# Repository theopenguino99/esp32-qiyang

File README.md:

<div align="center">

**On-device firmware for the crimp-ER hangboard scale — ESP32-C6, HX711 load cell, OLED readout &amp; live force streaming over BLE.**

</div>

---

# ESP32-C6 Smart Load Cell

Firmware for an ESP32-C6 based digital scale. Reads an HX711 load cell, shows live
weight on a 1.3" OLED, streams readings over BLE, and supports on-device
calibration with 2 push buttons. It speaks the **Tindeq Progressor** BLE protocol,
so it works with the official Tindeq app as well as the companion web app. I initially wanted to create an IOS app but realised I have to pay a premium to enroll in the Apple Developer Program in order to make the app public, so I made a web app instead which is free. My motivation for creating this project was to practice my software and hardware skills, and to build a useful tool for climbers. My gripe about the tindeq progressor is that it is quite expensive for what essentially is just a load cell so I decided to make one of my own and learn some skills along the way. This project was also something to keep me busy while I undergo ACL surgery rehabilitation. 

I would like to thank Yu Jie for helping me 3D print the prototype enclosure. I also want to thank [@SergioGasquez](https://github.com/SergioGasquez) for giving advice to build the device. I took quite a bit of inspiration from his project [Crimpdeq](https://github.com/crimpdeq).

Some important firmware modifications I made was to use a C6 module instead of a C3 rust module because I wanted to learn how to use a C6 for other future projects as it is one of the more powerful boards by espressif. Also I am using the platformio manager and writing the main firmware in arduino code simple for other beginner to intermediate developers. I also added 2 buttons for user friendly calibration if ever the user does not want to use the webapp or tindeq app. Also I implemented an OLED screen to visualise a force graph. Some things that I can potentially do in the future is a flappy bird game displayed on the OLED. These design choices were made with the possibility of further improvement without re-printing the PCB in mind. 

## Hardware

| Peripheral        | Connection                          |
|-------------------|-------------------------------------|
| HX711 load cell   | DT = GPIO11, SCK = GPIO10           |
| SH1106 OLED (I2C) | SDA = GPIO6, SCL = GPIO7, addr 0x3C |
| WS2812B RGB LED   | GPIO8 (onboard)                     |
| Button 1          | GPIO2 (active-low, internal pullup) |
| Button 2          | GPIO3 (active-low, internal pullup) |

All hardware design files live in [`hardware/`](hardware/) — KiCad project,
gerbers (`hardware/fab/`), and the 3D-printable enclosure.

### PCB

Custom 2-layer board designed in KiCad ([`hardware/pcb_Crimp-ER.kicad_pcb`](hardware/pcb_Crimp-ER.kicad_pcb)).

| Front | Back | Actual|
|:-----:|:----:|:-----:|
|  |  |  |

### Enclosure

Two-part 3D-printed case. Models (STL + STEP) live in
[`hardware/crimp-ER covers/`](hardware/crimp-ER%20covers/).

|Full Assembly| Top cover | Bottom cover |
|:---------:|:------------:|:-:|
||  |  |

> Print-ready downloads:
> [top STL](hardware/crimp-ER%20covers/top_cover.stl) ·
> [bottom STL](hardware/crimp-ER%20covers/bottom_cover.stl).

Two buttons drive the on-device UI: **Button 1 = change/skip**, **Button 2 =
OK/confirm**.

**On boot** the OLED shows a `CALIBRATE?` prompt and waits (no time limit) for a
choice:

- **Button 2** → run calibration (see below).
- **Button 1** → skip. If a calibration is saved, the device re-zeros the empty
  scale in memory (a boot tare that cancels power-on drift while keeping the saved
  scale factor); if none is saved, it warns and runs with defaults.

**Calibration**

1. *Pick the weight* — Button 1 cycles the reference-weight presets
   (1.25, 2.5, 5, 8, 10, 15, 20, 25 kg), Button 2 confirms. It starts at your
   last-used weight.
2. *Zero* — keep the scale empty; it samples the offset.
3. *Place weight* — a 30-second countdown appears (large timer + progress bar).
   Put the selected weight on the scale; Button 2 ends the countdown early.
4. The scale factor is computed and saved to flash (offset, scale, and the chosen
   weight), then a result screen shows (3 beeps on success, 1 on failure if the
   reading is invalid).

**Normal operation**

- OLED shows the current weight (large) plus a rolling history graph.
- The RGB LED flashes red while no BLE client is connected.
- Each changed reading is streamed over BLE as `"<weight> kg\n"`.

## BLE

The device advertises as **`Progressor_XXXX`** (`XXXX` derived from the chip MAC)
and exposes two services in parallel.

### Tindeq Progressor (works with the Tindeq app)

Emulates the Tindeq Progressor so the official **Tindeq app** can connect.

- Service: `7e4e1701-1ea6-40c9-9dcc-13d34ffead57`
- Data — notify, device → app: `7e4e1702-…`
- Control — write, app → device: `7e4e1703-…`
- **Weight stream** (little-endian): `[0x01][8][float32 kg][uint32 timestamp_µs]`,
  sent only between *start* and *stop*.
- **Commands:** tare `100`, start `101`, stop `102`, get app version `107`,
  get battery `111`. Tare is a soft, non-persisted re-zero (keeps the saved
  calibration factor).

### Nordic UART Service (web app)

- Service: `6E400001-…`, RX `6E400002-…`, TX `6E400003-…`
- Plain-text TX `"<weight> kg\n"`. Still running, so the companion web app works
  with no changes — it picks devices with `acceptAllDevices`, so the device simply
  shows up as `Progressor_XXXX` (instead of `ESP32-C6`) in the Bluetooth chooser.

A companion web app lives at `../esp32-qiyang-webapp`.

## Build & flash

```bash
pio run -t upload      # build + flash
pio device monitor     # serial @ 115200
pio run                # build only
```

## Licence

This project is dual-licensed by component:

- **Firmware** (`src/`, `include/`) — [MIT](LICENSE).
- **Hardware** (`hardware/`: PCB, gerbers, enclosure) —
  [CERN-OHL-S v2](hardware/LICENSE) (Strongly Reciprocal). See
  [hardware/README.md](hardware/README.md) for the notice.

In both cases please keep the copyright notice and credit theopenguino99.

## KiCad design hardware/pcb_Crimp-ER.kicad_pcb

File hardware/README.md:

# Hardware

PCB and enclosure design files for the esp32-qiyang smart scale.

- `pcb_Crimp-ER.kicad_{pro,sch,pcb}` — KiCad project (schematic + layout).
- `fab/` — gerbers, drill files, pick-and-place, fabrication zip.
- `crimp-ER covers/` — 3D-printed enclosure (`*.stl` + `*.step`).
- `renders/` — PNG/JPEG previews.

## Licence

Copyright theopenguino99.

This hardware design is licensed under the CERN Open Hardware Licence
Version 2 - Strongly Reciprocal (CERN-OHL-S v2). You may redistribute and
modify it under the terms of that licence; you must keep this notice and
distribute the Complete Source of any conveyed modifications under the same
licence. See [LICENSE](LICENSE) for the full text, or
<https://cern.ch/cern-ohl> for more information.

This design is distributed WITHOUT ANY EXPRESS OR IMPLIED WARRANTY,
INCLUDING OF MERCHANTABILITY, SATISFACTORY QUALITY AND FITNESS FOR A
PARTICULAR PURPOSE. Please see section 6 of the licence for details.

> Note: this licence applies to the **hardware design files in this
> directory only**. The firmware (`src/`, `include/`) is licensed under MIT —
> see the [root LICENSE](../LICENSE).

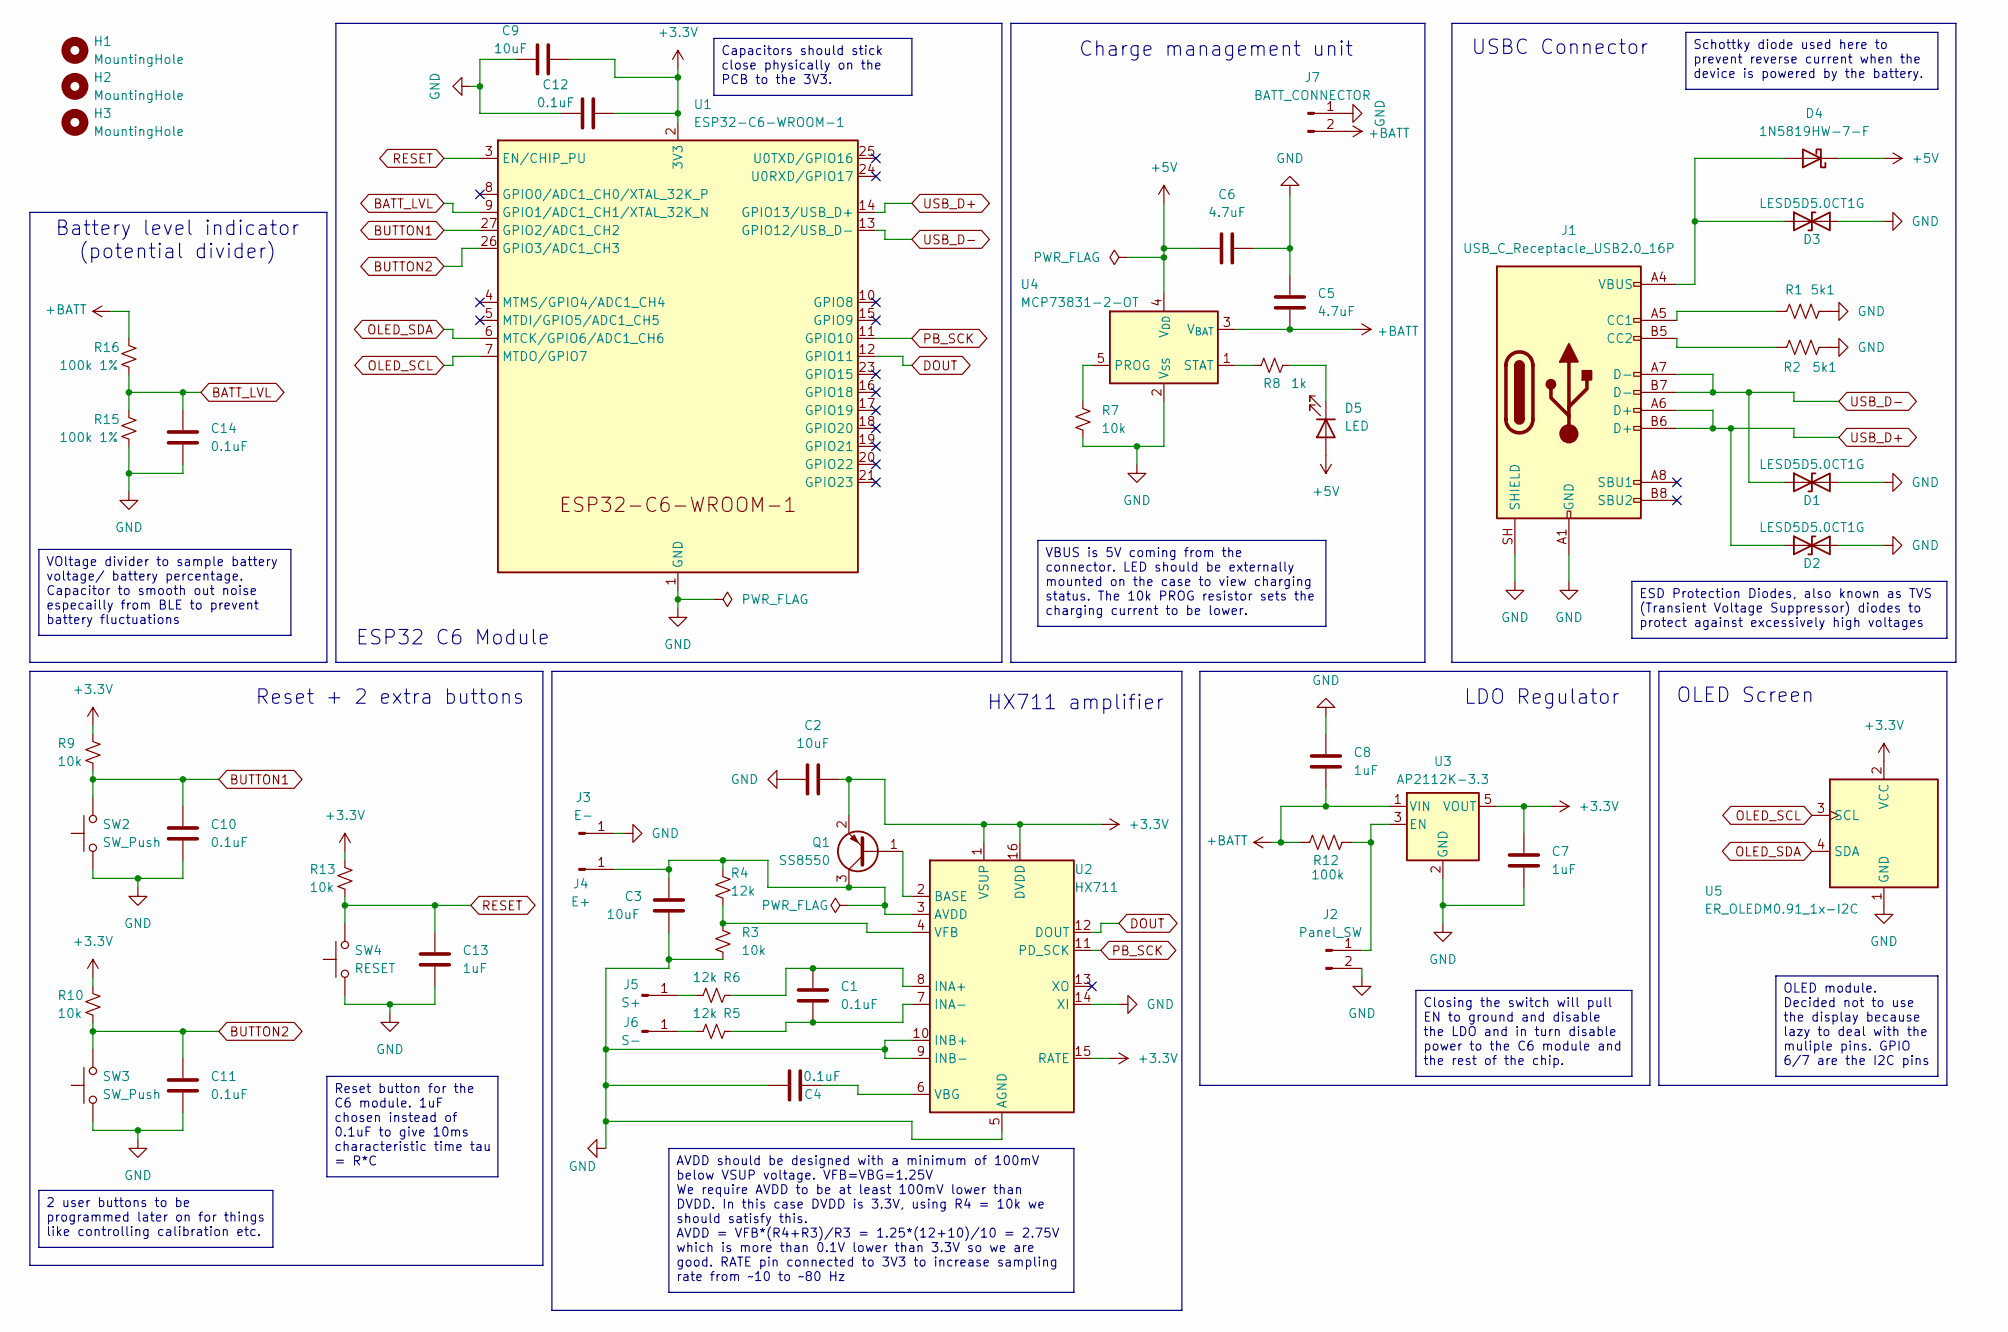
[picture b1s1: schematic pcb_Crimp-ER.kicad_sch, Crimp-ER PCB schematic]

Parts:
C1, C4, C10, C11, C12, C14: 0.1uF; C_0402_1005Metric
C2, C3, C9: 10uF; C_0603_1608Metric
C5, C6: 4.7uF; C_0603_1608Metric
C7, C8, C13: 1uF; C_0402_1005Metric
D1, D2, D3: LESD5D5.0CT1G; D_SOD-523
D4: 1N5819HW-7-F; D_SOD-123
D5: LED; PinSocket_1x02_P2.54mm_Vertical
H1, H2, H3: MountingHole; MountingHole_2.2mm_M2_DIN965_Pad
J1: USB_C_Receptacle_USB2.0_16P; USB_C_Receptacle_GCT_USB4105-xx-A_16P_TopMnt_Horizontal
J2: Panel_SW; PinSocket_1x02_P2.54mm_Vertical
J3: E-; PinSocket_1x01_P2.54mm_Vertical
J4: E+; PinSocket_1x01_P2.54mm_Vertical
J5: S+; PinSocket_1x01_P2.54mm_Vertical
J6: S-; PinSocket_1x01_P2.54mm_Vertical
J7: BATT_CONNECTOR; PinSocket_1x02_P2.54mm_Vertical
Q1: SS8550; SOT-23
R1, R2: 5k1; R_0402_1005Metric
R3, R7, R9, R10, R13: 10k; R_0402_1005Metric
R4, R5, R6: 12k; R_0402_1005Metric
R8: 1k; R_0402_1005Metric
R12: 100k; R_0402_1005Metric
R15, R16: 100k 1%; R_0402_1005Metric
SW2, SW3: SW_Push; PinSocket_1x02_P2.54mm_Vertical
SW4: RESET; PinSocket_1x02_P2.54mm_Vertical
U1: ESP32-C6-WROOM-1
U2: HX711; SOIC-16_3.9x9.9mm_P1.27mm
U3: AP2112K-3.3; SOT-23-5
U4: MCP73831-2-OT; SOT-23-5
U5: ER_OLEDM0.91_1x-I2C; PinSocket_1x04_P2.54mm_Vertical

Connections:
+3.3V: C2.2, C7.2, C9.1, C12.1, Q1.2 (E), R9.1, R10.1, R13.1, U1.2 (3V3), U2.1 (VSUP), U2.15 (RATE), U2.16 (DVDD), U3.5 (VOUT), U5.2 (VCC)
+5V: C6.2, D4.1 (K), D5.2 (A), U4.4 (V_{DD})
+BATT: C5.1, C8.1, J7.2, R12.1, R16.1, U3.1 (VIN), U4.3 (V_{BAT})
BATT_LVL: C14.1, R15.1, R16.2, U1.9 (GPIO1/ADC1_CH1/XTAL_32K_N)
BUTTON1: C10.1, R9.2, SW2.2, U1.27 (GPIO2/ADC1_CH2)
BUTTON2: C11.1, R10.2, SW3.2, U1.26 (GPIO3/ADC1_CH3)
DOUT: U1.12 (GPIO11), U2.12 (DOUT)
GND: C2.1, C3.2, C4.1, C5.2, C6.1, C7.1, C8.2, C9.2, C10.2, C11.2, C12.2, C13.2, C14.2, D1.2 (A2), D2.2 (A2), D3.2 (A2), J1.A1 (GND), J1.A12 (GND), J1.B1 (GND), J1.B12 (GND), J1.SH (SHIELD), J2.2, J3.1 (Pin_1_1), J7.1, R1.2, R2.2, R3.2, R7.2, R15.2, SW2.1, SW3.1, SW4.1, U1.1 (GND), U1.28 (GND), U1.29 (GND), U2.5 (AGND), U2.9 (INB-), U2.10 (INB+), U2.14 (XI), U3.2 (GND), U4.2 (V_{SS}), U5.1 (GND)
unnamed: D3.1 (A1), D4.2 (A), J1.A4 (VBUS), J1.A9 (VBUS), J1.B4 (VBUS), J1.B9 (VBUS)
unnamed: D5.1 (K), R8.2
unnamed: J1.A5 (CC1), R1.1
unnamed: J1.B5 (CC2), R2.1
unnamed: J2.1, R12.2, U3.3 (EN)
unnamed: C3.1, J4.1 (Pin_1_1), Q1.3 (C), R4.1, U2.3 (AVDD)
unnamed: J5.1 (Pin_1_1), R6.1
unnamed: J6.1 (Pin_1_1), R5.1
unnamed: Q1.1 (B), U2.2 (BASE)
unnamed: C1.1, R6.2, U2.8 (INA+)
unnamed: C1.2, R5.2, U2.7 (INA-)
unnamed: C4.2, U2.6 (VBG)
unnamed: R3.1, R4.2, U2.4 (VFB)
unnamed: R7.1, U4.5 (PROG)
unnamed: R8.1, U4.1 (STAT)
OLED_SCL: U1.7 (MTDO/GPIO7), U5.3 (SCL)
OLED_SDA: U1.6 (MTCK/GPIO6/ADC1_CH6), U5.4 (SDA)
PB_SCK: U1.11 (GPIO10), U2.11 (PD_SCK)
RESET: C13.1, R13.2, SW4.2, U1.3 (EN/CHIP_PU)
USB_D+: D2.1 (A1), J1.A6 (D+), J1.B6 (D+), U1.14 (GPIO13/USB_D+)
USB_D-: D1.1 (A1), J1.A7 (D-), J1.B7 (D-), U1.13 (GPIO12/USB_D-)

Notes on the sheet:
Reset + 2 extra buttons
LDO Regulator
HX711 amplifier
OLED Screen
ESP32 C6 Module
Battery level indicator (potential divider)
USBC Connector
Charge management unit
VBUS is 5V coming from the connector. LED should be externally mounted on the case to view charging status. The 10k PROG resistor sets the charging current to be lower.
2 user buttons to be programmed later on for things like controlling calibration etc.
Closing the switch will pull EN to ground and disable the LDO and in turn disable power to the C6 module and the rest of the chip.
AVDD should be designed with a minimum of 100mV below VSUP voltage. VFB=VBG=1.25V We require AVDD to be at least 100mV lower than DVDD. In this case DVDD is 3.3V, using R4 = 10k we should satisfy this. AVDD = VFB*(R4+R3)/R3 = 1.25*(12+10)/10 = 2.75V which is more than 0.1V lower than 3.3V so we are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
Schottky diode used here to prevent reverse current when the device is powered by the battery.
Reset button for the C6 module. 1uF chosen instead of 0.1uF to give 10ms characteristic time tau = R*C
ESD Protection Diodes, also known as TVS (Transient Voltage Suppressor) diodes to protect against excessively high voltages
OLED module. Decided not to use the display because lazy to deal with the muliple pins. GPIO 6/7 are the I2C pins
VOltage divider to sample battery voltage/ battery percentage. Capacitor to smooth out noise especailly from BLE to prevent battery fluctuations
Capacitors should stick close physically on the PCB to the 3V3.

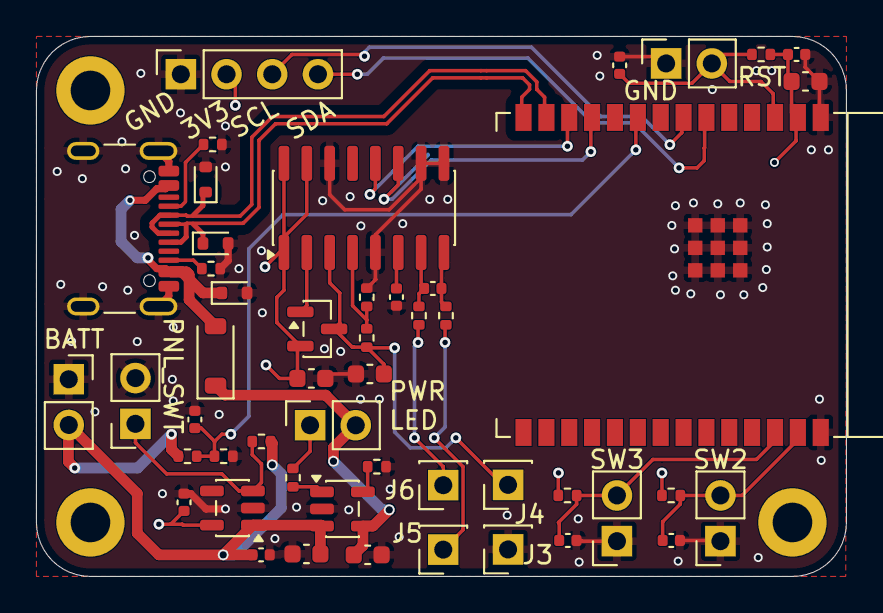
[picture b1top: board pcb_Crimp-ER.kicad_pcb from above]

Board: 4 copper layers, 45.0 x 30.0 mm, 52 parts (0 on the bottom side), 29 nets.

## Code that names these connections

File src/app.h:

#pragma once

// Single shared header for the whole firmware. Each .cpp includes just this
// file; it provides every constant, shared object, shared variable, and
// function prototype the modules need to see each other.

#include <Arduino.h>
#include <Wire.h>
#include <limits.h>
#include <string.h>
#include <math.h>
#include <Adafruit_NeoPixel.h>
#include <Adafruit_SH110X.h>
#include <HX711.h>
#include <Preferences.h>
#include <NimBLEDevice.h>

// ─── Pins ────────────────────────────────────────────────────────────────────
#define LED_PIN       8
#define NUM_LEDS      1
#define BUZZER_PIN    9
#define HX711_DT_PIN  11
#define HX711_SCK_PIN 10
#define BUTTON1_PIN   2
#define BUTTON2_PIN   3
#define BATT_ADC_PIN  1    // GPIO1 / ADC1_CH1 — battery sense (100k/100k divider, Vbatt = 2*Vadc)

// ─── OLED — SH1106 1.3" 128×64 ───────────────────────────────────────────────
#define OLED_ADDR   0x3C
#define OLED_WIDTH  128
#define OLED_HEIGHT 64
#define OLED_RESET  -1
#define OLED_SDA    6
#define OLED_SCL    7
#define OLED_UPDATE_MS 50   // 50ms refresh (cherry-picked from oled-display)

// ─── BLE (Nordic UART Service) — kept for the web app ────────────────────────
#define NUS_SERVICE_UUID "6E400001-B5A3-F393-E0A9-E50E24DCCA9E"
#define NUS_RX_UUID      "6E400002-B5A3-F393-E0A9-E50E24DCCA9E"
#define NUS_TX_UUID      "6E400003-B5A3-F393-E0A9-E50E24DCCA9E"

// ─── Tindeq Progressor BLE protocol — lets the official Tindeq app connect ────
// All multi-byte values are little-endian (ESP32 native), so float/uint32 can
// be memcpy'd straight into the packet.
#define TINDEQ_SERVICE_UUID "7e4e1701-1ea6-40c9-9dcc-13d34ffead57"
#define TINDEQ_DATA_UUID    "7e4e1702-1ea6-40c9-9dcc-13d34ffead57" // notify: device -> app
#define TINDEQ_CTRL_UUID    "7e4e1703-1ea6-40c9-9dcc-13d34ffead57" // write:  app -> device
// Control-point command opcodes (app -> device)
#define TINDEQ_CMD_TARE        100
#define TINDEQ_CMD_START_MEAS  101
#define TINDEQ_CMD_STOP_MEAS   102
#define TINDEQ_CMD_GET_APP_VER 107
#define TINDEQ_CMD_ENTER_SLEEP 110
#define TINDEQ_CMD_GET_BATT    111
// Notification response codes (device -> app)
#define TINDEQ_RES_CMD     0x00  // command response (battery / version / ...)
#define TINDEQ_RES_WEIGHT  0x01  // weight sample: float32 kg + uint32 timestamp_us

// ─── Calibration ─────────────────────────────────────────────────────────────
#define CALIB_WEIGHT_KG   10.0f  // default reference weight; user-selectable at calibration
#define CALIB_SAMPLES     10
#define CALIB_COUNTDOWN_S 30     // seconds to place known weight
#define DEBOUNCE_MS       50

// ─── Signal filtering ────────────────────────────────────────────────────────
// Median window rejects impulsive spikes with ~no lag — applied to every consumer
// (display + BLE), so it won't distort Tindeq RFD. The display EMA is extra
// smoothing for the OLED readout/graph ONLY; the BLE streams stay unfiltered by it.
#define FILTER_MEDIAN_WINDOW 3      // odd; raw samples kept for the running median
#define DISPLAY_EMA_ALPHA    0.2f   // OLED-only smoothing (0..1; higher = snappier, less smooth)

// ─── Battery monitor — GPIO1/ADC1_CH1 via a 100k/100k divider (Vbatt = 2*Vadc) ─
#define BATT_FULL_MV   4200   // 1S LiPo fully charged (CC/CV terminates at 4.2V) → 100%
#define BATT_EMPTY_MV  3500   // AP2112K-3.3 brown-out floor (3.3V + ~200mV dropout) → 0%
#define BATT_READ_MS   2000   // sampling cadence
#define BATT_SAMPLES   8      // ADC reads averaged per update

// ─── Shared peripheral objects (hardware.cpp) ────────────────────────────────
extern Adafruit_NeoPixel led;
extern Adafruit_SH1106G  display;
extern HX711             scale;
extern Preferences       prefs;

// ─── Input (input.cpp) ───────────────────────────────────────────────────────
bool buttonPressed(int pin = BUTTON1_PIN);   // debounced active-low read
void waitButtonRelease(int pin = BUTTON1_PIN);
void beepCount(int n);

// ─── Battery (battery.cpp) ───────────────────────────────────────────────────
extern uint32_t batteryMv;   // measured battery voltage (mV)
extern int      batteryPct;  // 0..100, derived from batteryMv
void updateBattery();

// ─── Calibration (calibration.cpp) ───────────────────────────────────────────
// Model: weightKg = (raw - calOffset) * calScale. Persisted to flash
// (Preferences namespace "hx711", keys "offset"/"scale"/"calwt").
extern float calOffset;
extern float calScale;
extern float calWeight;      // selected reference weight, persisted to flash
bool  loadCalibration();     // true if offset+scale were found in flash
void  saveCalibration();
float readRawAverage(int samples);
void  selectCalibWeight();   // weight-preset chooser (blocking, boot-only)
void  runCalibration();      // full boot calibration flow
float medianFilteredKg(long raw);  // running median of raw counts → calibrated kg (spike rejection)

// ─── OLED screens (ui.cpp) ───────────────────────────────────────────────────
void showCalibPrompt();
void showInfo(const char* title, const char* line1,
              const char* line2 = nullptr, const char* line3 = nullptr);
void showCountdown(int secsLeft);
void showCalibResult(bool ok);
void showCalWeightSelect(float w);
void updateDisplay(float weightKg);

// ─── BLE services (ble_service.cpp) ──────────────────────────────────────────
extern bool deviceConnected;            // a central is connected (NUS gate)
extern NimBLECharacteristic* pTxChar;   // NUS TX notify characteristic
extern bool          tindeqMeasuring;   // streaming between START(101)/STOP(102)
extern bool          tindeqTareReq;     // TARE(100) requested, serviced in loop()
extern unsigned long measureStartMicros;// micros() at START, for sample timestamps
void tindeqNotifyWeight(float kg, uint32_t tsMicros);
void bleSetup();

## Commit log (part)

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2026-04-19 Serial monitor reads load cell
2026-04-20 feat: map load cell pressure to LED
2026-04-23 debug: broadcast name settings
    Explicitly include ESP32-C6 name so that the webapp can view the device
2026-05-11 feat: enhance OLED display functionality and add I2C initialization
2026-06-01 Added images of 3D kicad design
2026-06-12 feat: add Adafruit GFX and SH110X libraries for OLED display support
2026-06-12 docs: add CLAUDE.md for project guidance and firmware details
2026-06-13 docs: enhance CLAUDE.md and README.md with Tindeq Progressor protocol details
2026-06-13 feat: add button2 functionality for calibration and weight selection
2026-06-14 feat: update .gitignore for KiCad files and add new directories for hardware assets
2026-06-14 Refactor code structure for improved readability and maintainability
2026-06-14 feat: update documentation and add hardware design files for buttons and enclosure
2026-06-14 feat: enhance calibration process and update README for two-button functionality
2026-06-14 feat: implement battery monitoring and display indicator
2026-06-14 docs: update README with project motivation, hardware choices, and licensing details
2026-06-22 Add new STL file for top cover v2 of crimp-ER covers
2026-06-22 chore: update platformio.ini to pin upload and monitor ports for USB communication
2026-06-22 chore: update platformio.ini to specify upload and monitor ports for USB communication
2026-06-22 Add calibration functionality and UI improvements
    - Implement calibration logic in `calibration.cpp` for offset and scale adjustments.
    - Create `hardware.cpp` to initialize hardware components including LED, display, and scale.
    - Move button handling functions to `input.cpp` for better organization.
    - Refactor main loop in `main.ino` to utilize new setup functions and improve readability.
    - Introduce `ui.cpp` for display-related functions, enhancing the user interface for calibration prompts and weight displays.
    - Implement history tracking for weight measurements in the display.
2026-06-22 Add median filtering and EMA smoothing for weight readings
